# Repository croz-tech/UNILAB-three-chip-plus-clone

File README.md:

# UNILAB three-chip-plus-clone
**A clone of the main UNILAB 6502 learning board, part number 540.300**<BR><BR>
Features & changes over the [original UNILAB educational system](http://retro.hansotten.nl/6502-sbc/three-chips-plus/):
- Compatible with 6502/6522 or newer 65C02/65C22 fully static parts
- 1Mhz crystal replaced with oscillator module (more readily available)
- Internal/external clock selectable by jumper
- Address bus, Data bus, R/W and Clock available on headers to be compatible with [Ben Eater](https://eater.net/6502)'s [Arduino Mega Moitor](https://eater.net/downloads/6502-monitor.ino)
- Compatible with original three-chip-plus I/O peripheral boards, Program Memory Board, and Program Loader
- Original PCB form factor (yes, rather large by today's standards but I went for originality
- **See note at bottom of this page for ISS1 (ONLY ISS1) board error and modification**

## Assembled PCB (ISS1):

## Schematic (ISS2):

## ERROR and correction for ISS1 schematic and PCB
Note: there are two errors on the ISS1 **ONLY** schematic and boards, these are fixed on ISS2 in the design:
1) Polarity of POWER IN is reversed on the PCB legend (but correctly diode-protected)
2) Clock error, where U4 (the 6522 pin 25) should be driven with PHI2 (same phase as U5, the 6502) and U2 pins 2,10,12 should be driven with ~PHI2 (inverted phase compared to the 6502 and 6522).  Correcting this involves two track breaks and two wires being fitted to the PCB as below (one on the component-side below the socket of U3, one on the solder-side):

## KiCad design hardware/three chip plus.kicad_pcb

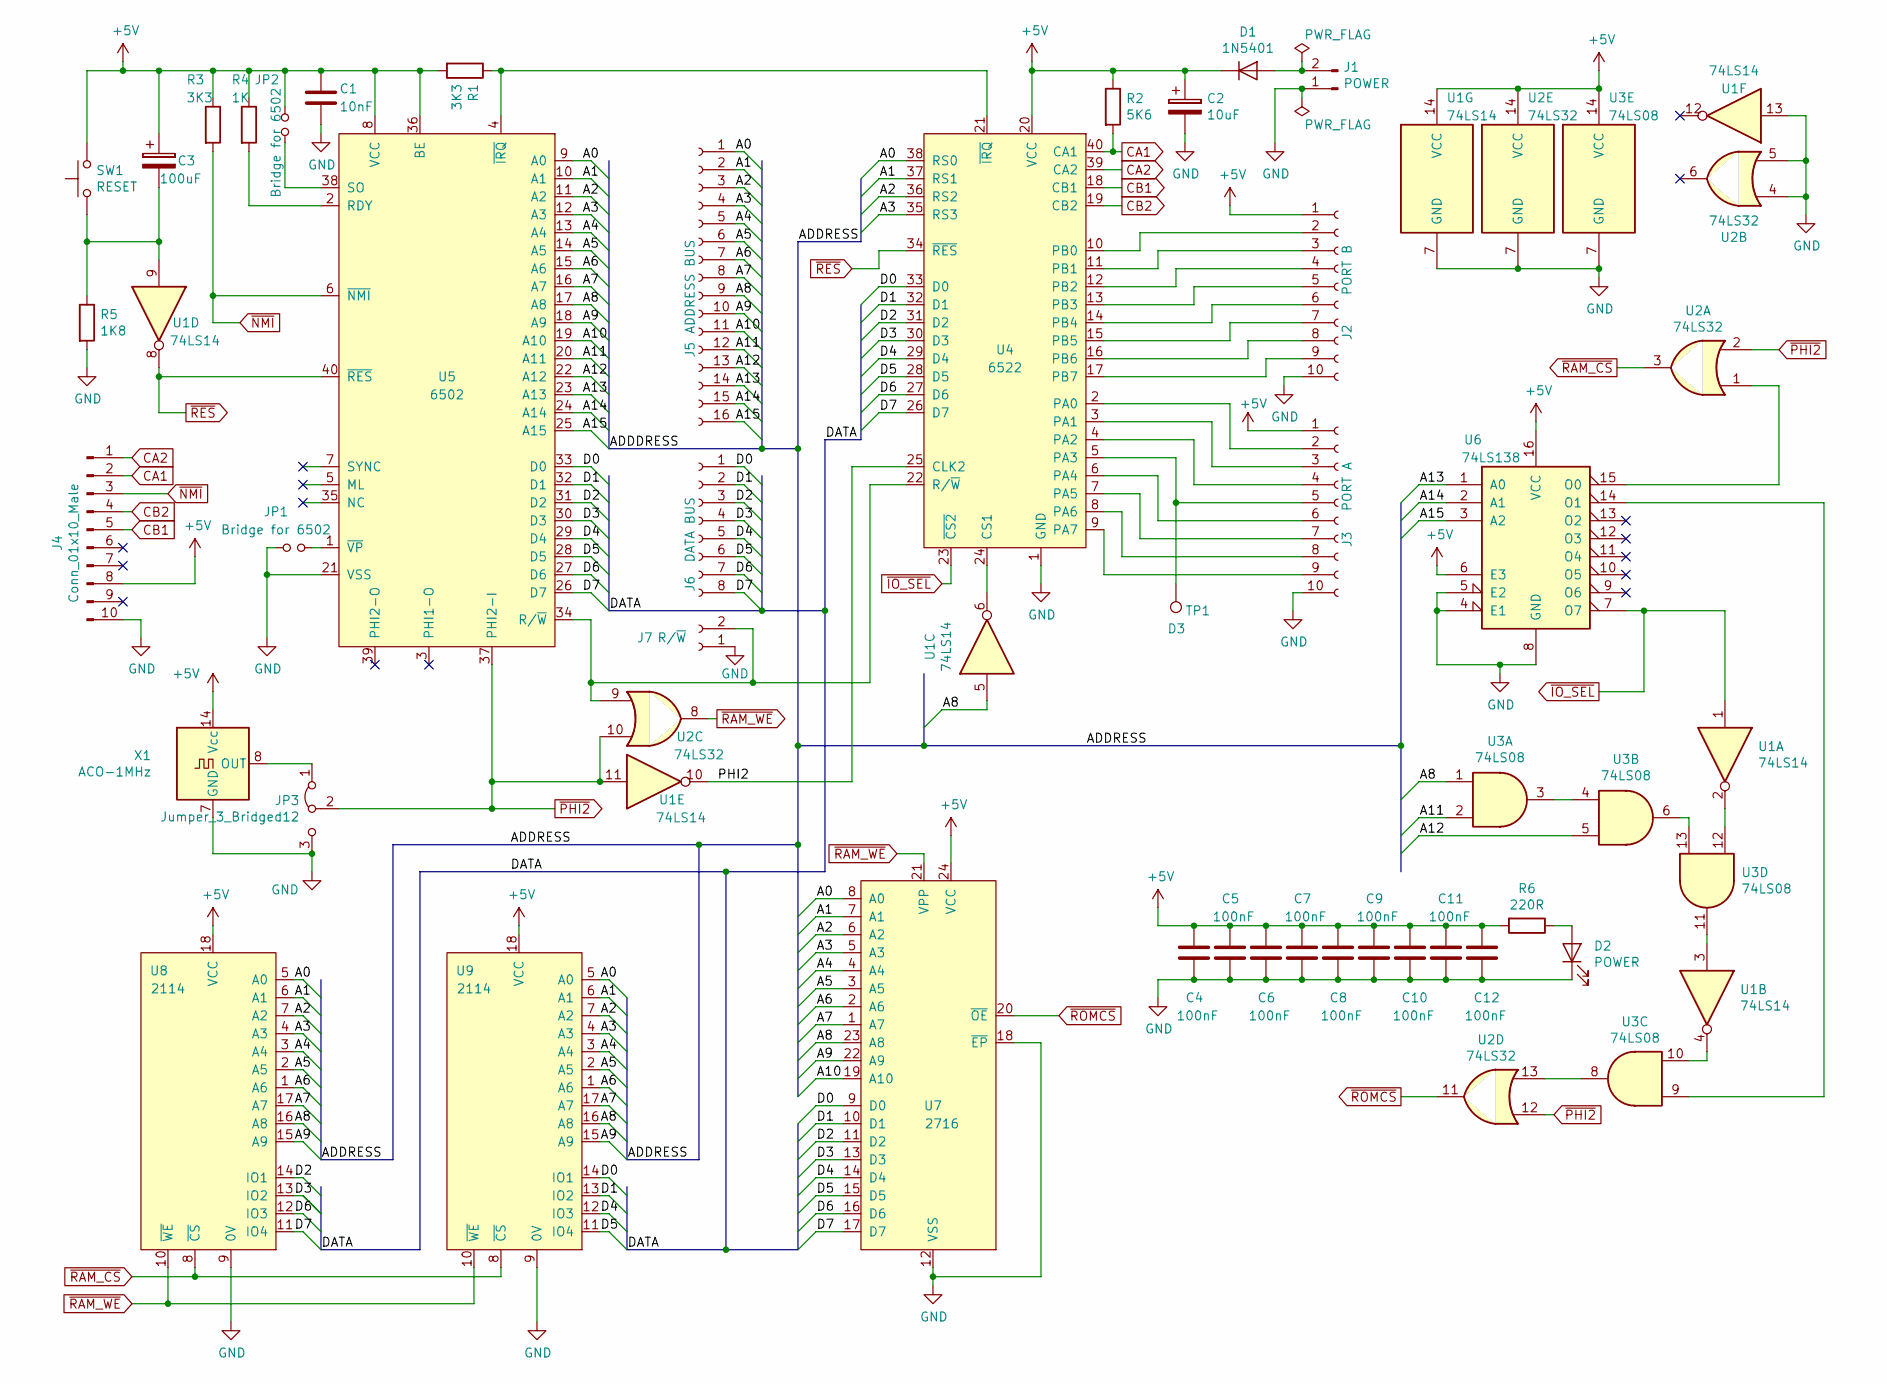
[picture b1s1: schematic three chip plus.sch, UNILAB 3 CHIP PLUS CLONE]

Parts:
C1: 10nF; C_Rect_L7.2mm_W2.5mm_P5.00mm_FKS2_FKP2_MKS2_MKP2
C2: 10uF; CP_Radial_D4.0mm_P1.50mm
C3: 100uF; CP_Radial_D5.0mm_P2.00mm
C4, C5, C6, C7, C8, C9, C10, C11, C12: 100nF; C_Rect_L7.2mm_W2.5mm_P5.00mm_FKS2_FKP2_MKS2_MKP2
D1: 1N5401; D_DO-201AD_P12.70mm_Horizontal
D2: POWER; LED_D3.0mm
J1: POWER; PinHeader_1x02_P2.54mm_Vertical
J2: PORT B; 10W_RA_Female
J3: PORT A; 10W_RA_Female
J4: Conn_01x10_Male; PinHeader_1x10_P2.54mm_Vertical
J5: ADDRESS BUS; PinHeader_1x16_P2.54mm_Vertical
J6: DATA BUS; PinHeader_1x08_P2.54mm_Vertical
J7: R/~W; PinHeader_1x02_P2.54mm_Vertical
JP1, JP2: Bridge for 6502; PinHeader_1x02_P2.54mm_Vertical
JP3: Jumper_3_Bridged12; PinHeader_1x03_P2.54mm_Vertical
R1, R3: 3K3; R_Axial_DIN0207_L6.3mm_D2.5mm_P10.16mm_Horizontal
R2: 5K6; R_Axial_DIN0207_L6.3mm_D2.5mm_P10.16mm_Horizontal
R4: 1K; R_Axial_DIN0207_L6.3mm_D2.5mm_P10.16mm_Horizontal
R5: 1K8; R_Axial_DIN0207_L6.3mm_D2.5mm_P10.16mm_Horizontal
R6: 220R; R_Axial_DIN0207_L6.3mm_D2.5mm_P10.16mm_Horizontal
SW1: RESET; SW_PUSH_6mm
TP1: D3; PinHeader_1x01_P2.54mm_Vertical
U1: 74LS14; DIP-14_W7.62mm_LongPads
U2: 74LS32; DIP-14_W7.62mm_LongPads
U3: 74LS08; DIP-14_W7.62mm_LongPads
U4: 6522; DIP-40_W15.24mm_Socket_LongPads
U5: 6502; DIP-40_W15.24mm_Socket_LongPads
U6: 74LS138; DIP-16_W7.62mm_LongPads
U7: 2716; DIP-24_W15.24mm_Socket_LongPads_ZIF
U8, U9: 2114; DIP-18_W7.62mm_LongPads
X1: ACO-1MHz; Oscillator_DIP-14

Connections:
/A0: J5.1, U4.38 (RS0), U5.9 (A0), U7.8 (A0), U8.5 (A0), U9.5 (A0)
/A1: J5.2, U4.37 (RS1), U5.10 (A1), U7.7 (A1), U8.6 (A1), U9.6 (A1)
/A2: J5.3, U4.36 (RS2), U5.11 (A2), U7.6 (A2), U8.7 (A2), U9.7 (A2)
/A3: J5.4, U4.35 (RS3), U5.12 (A3), U7.5 (A3), U8.4 (A3), U9.4 (A3)
/A4: J5.5, U5.13 (A4), U7.4 (A4), U8.3 (A4), U9.3 (A4)
/A5: J5.6, U5.14 (A5), U7.3 (A5), U8.2 (A5), U9.2 (A5)
/A6: J5.7, U5.15 (A6), U7.2 (A6), U8.1 (A6), U9.1 (A6)
/A7: J5.8, U5.16 (A7), U7.1 (A7), U8.17 (A7), U9.17 (A7)
/A8: J5.9, U1.5, U3.1, U5.17 (A8), U7.23 (A8), U8.16 (A8), U9.16 (A8)
/A9: J5.10, U5.18 (A9), U7.22 (A9), U8.15 (A9), U9.15 (A9)
/A10: J5.11, U5.19 (A10), U7.19 (A10)
/A11: J5.12, U3.2, U5.20 (A11)
/A12: J5.13, U3.5, U5.22 (A12)
/A13: J5.14, U5.23 (A13), U6.1 (A0)
/A14: J5.15, U5.24 (A14), U6.2 (A1)
/A15: J5.16, U5.25 (A15), U6.3 (A2)
/D0: J6.1, U4.33 (D0), U5.33 (D0), U7.9 (D0), U9.14 (IO1)
/D1: J6.2, U4.32 (D1), U5.32 (D1), U7.10 (D1), U9.13 (IO2)
/D2: J6.3, U4.31 (D2), U5.31 (D2), U7.11 (D2), U8.14 (IO1)
/D3: J6.4, U4.30 (D3), U5.30 (D3), U7.13 (D3), U8.13 (IO2)
/D4: J6.5, U4.29 (D4), U5.29 (D4), U7.14 (D4), U9.12 (IO3)
/D5: J6.6, U4.28 (D5), U5.28 (D5), U7.15 (D5), U9.11 (IO4)
/D6: J6.7, U4.27 (D6), U5.27 (D6), U7.16 (D6), U8.12 (IO3)
/D7: J6.8, U4.26 (D7), U5.26 (D7), U7.17 (D7), U8.11 (IO4)
CA1: J4.2, R2.2, U4.40 (CA1)
CA2: J4.1, U4.39 (CA2)
CB1: J4.5, U4.18 (CB1)
CB2: J4.4, U4.19 (CB2)
unnamed: C3.2, R5.1, SW1.1, U1.9
unnamed: D2.2 (A), R6.1
unnamed: J2.2, U4.10 (PB0)
unnamed: J2.3, U4.11 (PB1)
unnamed: J2.4, U4.12 (PB2)
unnamed: J2.5, U4.13 (PB3)
unnamed: J2.6, U4.14 (PB4)
unnamed: J2.7, U4.15 (PB5)
unnamed: J2.8, U4.16 (PB6)
unnamed: J2.9, U4.17 (PB7)
unnamed: J3.2, U4.2 (PA0)
unnamed: J3.3, U4.3 (PA1)
unnamed: J3.4, U4.4 (PA2)
unnamed: J3.5, TP1.1, U4.5 (PA3)
unnamed: J3.6, U4.6 (PA4)
unnamed: J3.7, U4.7 (PA5)
unnamed: J3.8, U4.8 (PA6)
unnamed: J3.9, U4.9 (PA7)
unnamed: J7.2, U2.9, U4.22 (R/~W), U5.34 (R/~W)
unnamed: JP1.2, U5.1 (~VP)
unnamed: JP2.2, U5.38 (SO)
unnamed: JP3.1 (A), X1.8 (OUT)
unnamed: R1.1, U4.21 (~IRQ), U5.4 (~IRQ)
unnamed: R4.2, U5.2 (RDY)
unnamed: U1.2, U3.12
unnamed: U1.3, U3.11
unnamed: U1.4, U3.10
unnamed: U1.6, U4.24 (CS1)
unnamed: U2.1, U6.15 (O0)
unnamed: U2.13, U3.8
unnamed: U3.3, U3.4
unnamed: U3.9, U6.14 (O1)
unnamed: U3.6, U3.13
~IO_SEL: U1.1, U4.23 (~CS2), U6.7 (O7)
~NMI: J4.3, R3.2, U5.6 (~NMI)
~RAM_CS: U2.3, U8.8 (~CS), U9.8 (~CS)
~RAM_WE: U2.8, U7.21 (VPP), U8.10 (~WE), U9.10 (~WE)
~RES: U1.8, U4.34 (~RES), U5.40 (~RES)
~ROMCS: U2.11, U7.20 (~OE)

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
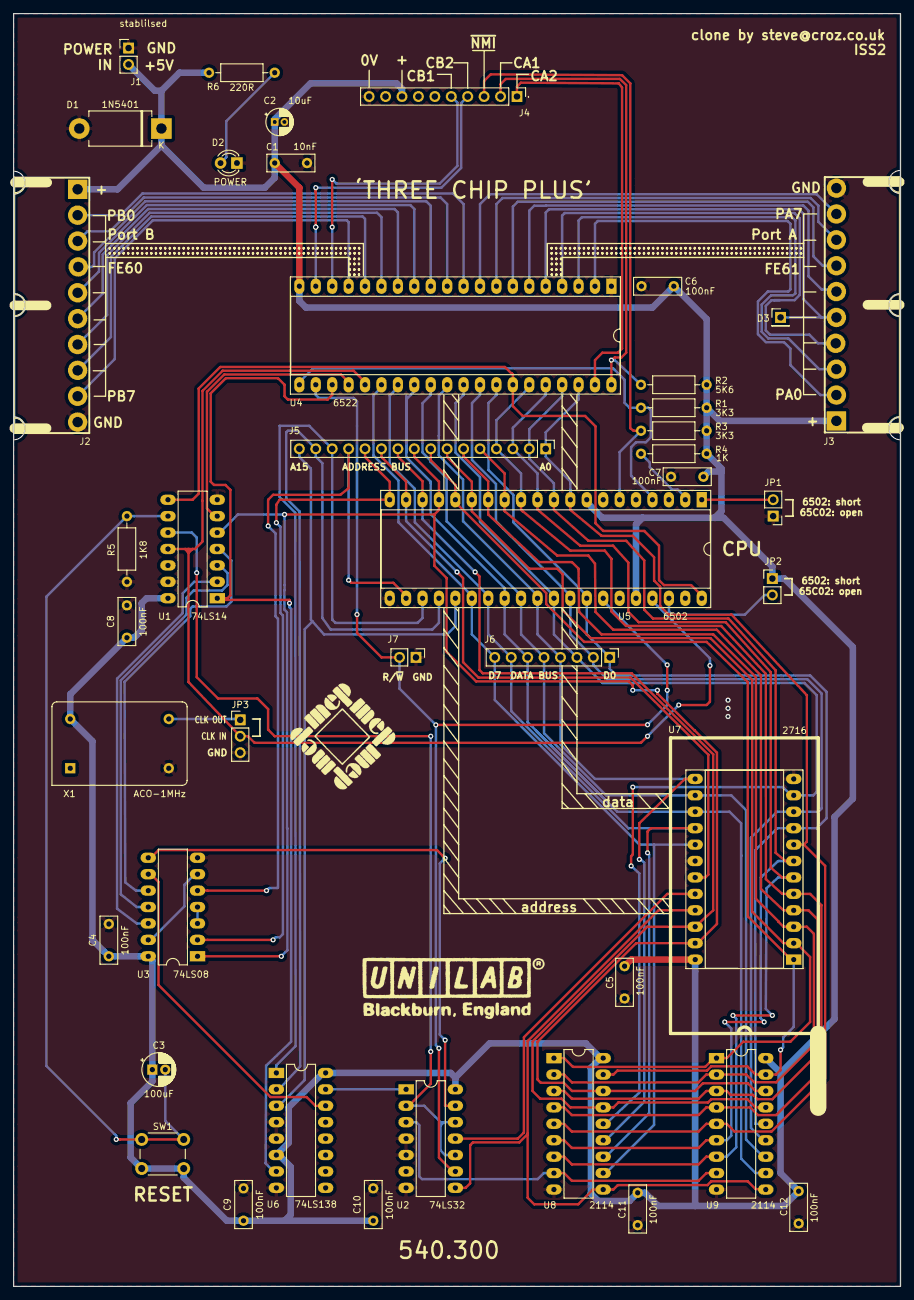
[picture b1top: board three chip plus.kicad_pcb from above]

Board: 2 copper layers, 137.2 x 196.8 mm, 42 parts (0 on the bottom side), 71 nets.

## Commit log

2021-05-31 Initial revision
    Initial revision design: schematics, symbols, footprints and board
2021-05-31 ISS2 Updates
    Change log:
    1. corrected error in PHI2/~PHI2~ clocks to U4 and U2 (schematic & PCB)
    2. made D1 parallel protection to avoid volt drop on +5V rail
    3. added missing R5, C2 legends (PCB)
    4. corrected Power In legend polarity (PCB)
2021-05-31 Update README.md
    Updated to show new schematic and that modifications necessary for ISS1 only
